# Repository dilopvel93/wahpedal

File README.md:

# wahpedal
Files backup of the Crybaby clone pedal project. Feel free to lurk around.

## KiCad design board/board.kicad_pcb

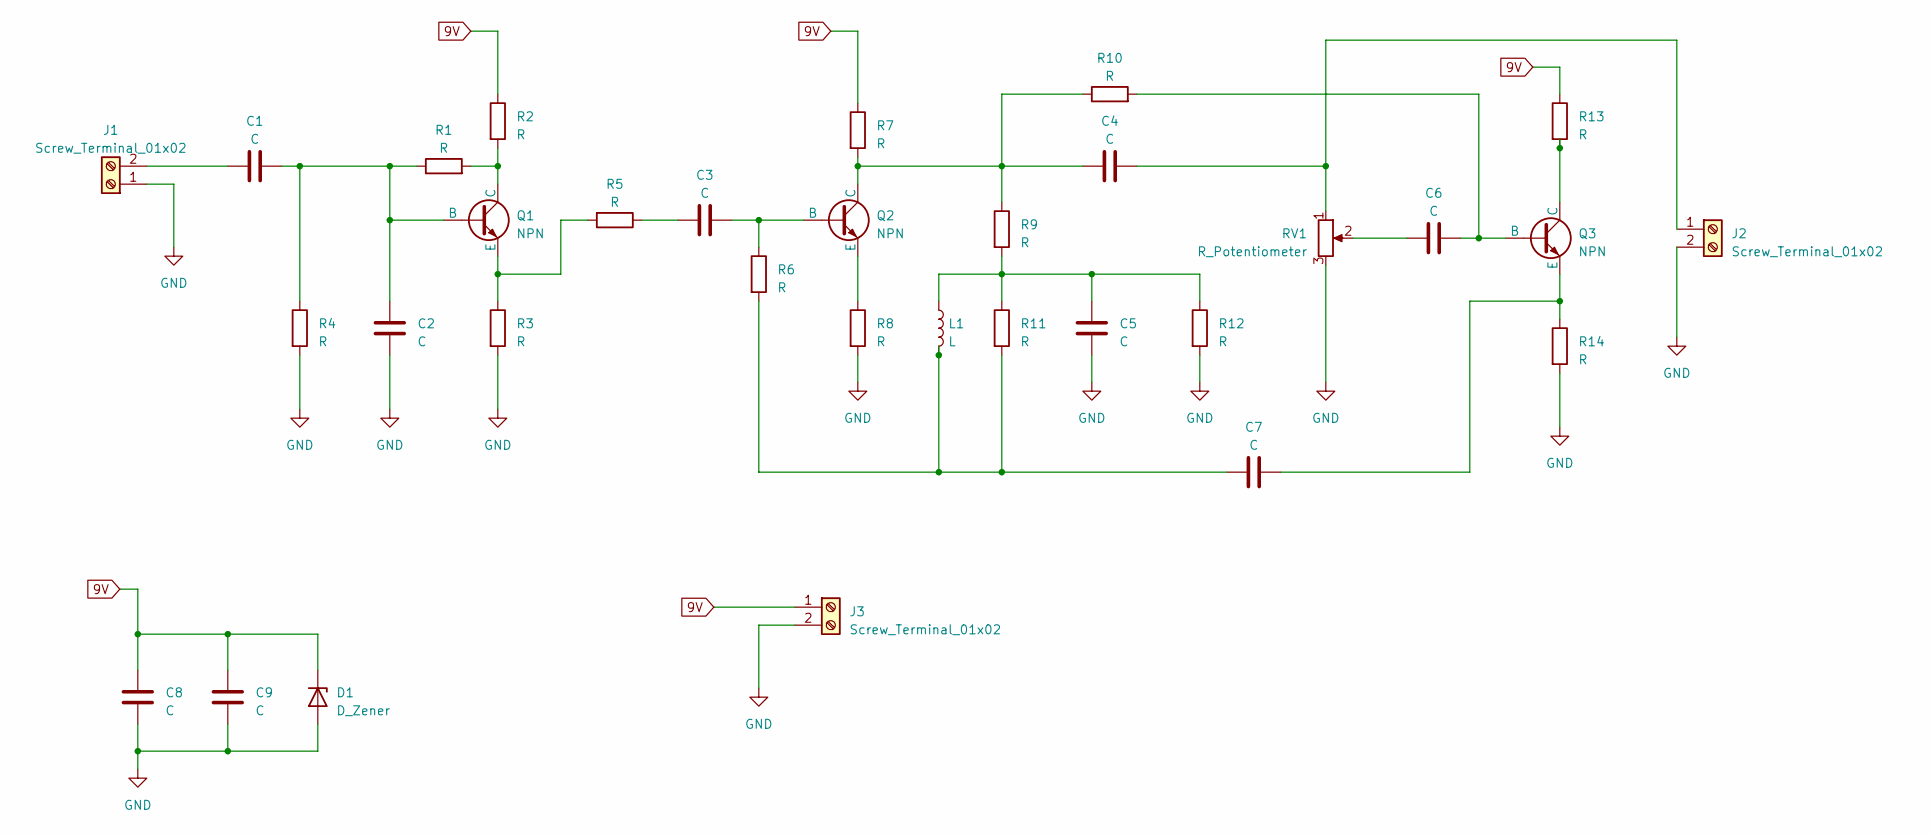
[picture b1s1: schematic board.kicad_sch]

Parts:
C1, C2, C3, C4, C5, C6, C7, C8, C9: C; CP_Radial_D8.0mm_P5.00mm
D1: D_Zener; D_DO-41_SOD81_P10.16mm_Horizontal
J1, J2, J3: Screw_Terminal_01x02; TerminalBlock_4Ucon_1x02_P3.50mm_Horizontal
L1: L; L_Radial_D16.8mm_P12.70mm_Vishay_IHB-1
Q1, Q2, Q3: NPN; TO-92
R1, R2, R3, R4, R5, R6, R7, R8, R9, R10, R11, R12, R13, R14: R; R_Axial_DIN0309_L9.0mm_D3.2mm_P15.24mm_Horizontal
RV1: R_Potentiometer; Wuerth_WR-WTB_64800311622_1x03_P1.50mm_Vertical

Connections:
9V: C8.1, C9.1, D1.1 (K), J3.1, R2.1, R7.1, R13.1
GND: C2.2, C5.2, C8.2, C9.2, D1.2 (A), J1.1, J2.2, J3.2, R3.2, R4.2, R8.2, R12.2, R14.2, RV1.3
unnamed: C3.1, R5.1
unnamed: C5.1, L1.1, R9.2, R11.1, R12.1
unnamed: C6.1, RV1.2
unnamed: C7.1, L1.2, R6.2, R11.2
unnamed: C1.1, J1.2
unnamed: C4.2, J2.1, RV1.1
unnamed: C1.2, C2.1, Q1.2 (B), R1.1, R4.1
unnamed: Q1.1 (C), R1.2, R2.2
unnamed: Q1.3 (E), R3.1, R5.2
unnamed: C3.2, Q2.2 (B), R6.1
unnamed: C4.1, Q2.1 (C), R7.2, R9.1, R10.1
unnamed: Q2.3 (E), R8.1
unnamed: C6.2, Q3.2 (B), R10.2
unnamed: Q3.1 (C), R13.2
unnamed: C7.2, Q3.3 (E), R14.1

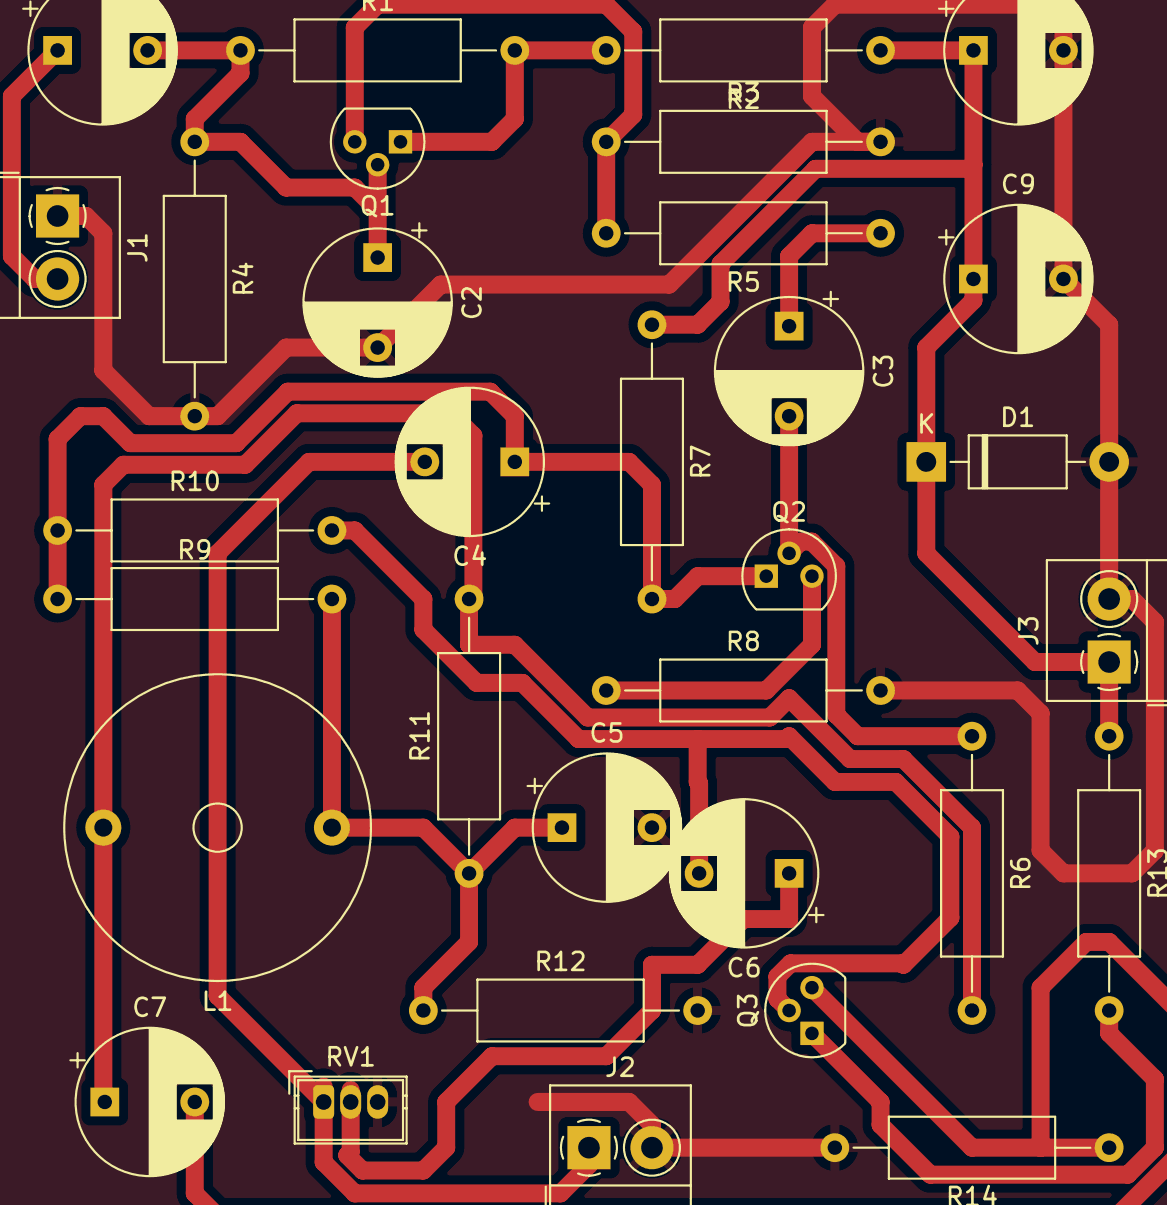
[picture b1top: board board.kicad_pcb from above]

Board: 2 copper layers, 32 parts (0 on the bottom side), 17 nets.

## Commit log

2023-04-21 Created KiCAD PCB project
2023-04-21 Started input buffer stage
2023-04-24 Added some components
2023-07-09 Complete schematic
2023-07-09 Assigned footprints to schematic symbols
2023-07-09 Updates PCB file
2023-07-14 Completed board layout
2023-07-14 Corrected ground plane defect
